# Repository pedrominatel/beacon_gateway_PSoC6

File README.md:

# Beacon Gateway using PSoC6

Beacon Gateway Based on the PSoC6 from CYPRESS

[See this project at Hackaday](https://hackaday.io/project/171521-bluetooth-beacon-proximity-gateway)

### To solve the TLS Proxy error on Ubuntu 20.04 see the link below:

[Use this as starting point](https://github.com/cypresssemiconductorco/mtb-example-anycloud-ble-multi-beacon/blob/f9b318d08451e1a02660163477f669e5317bccea/configs/app_bt_cfg.c)

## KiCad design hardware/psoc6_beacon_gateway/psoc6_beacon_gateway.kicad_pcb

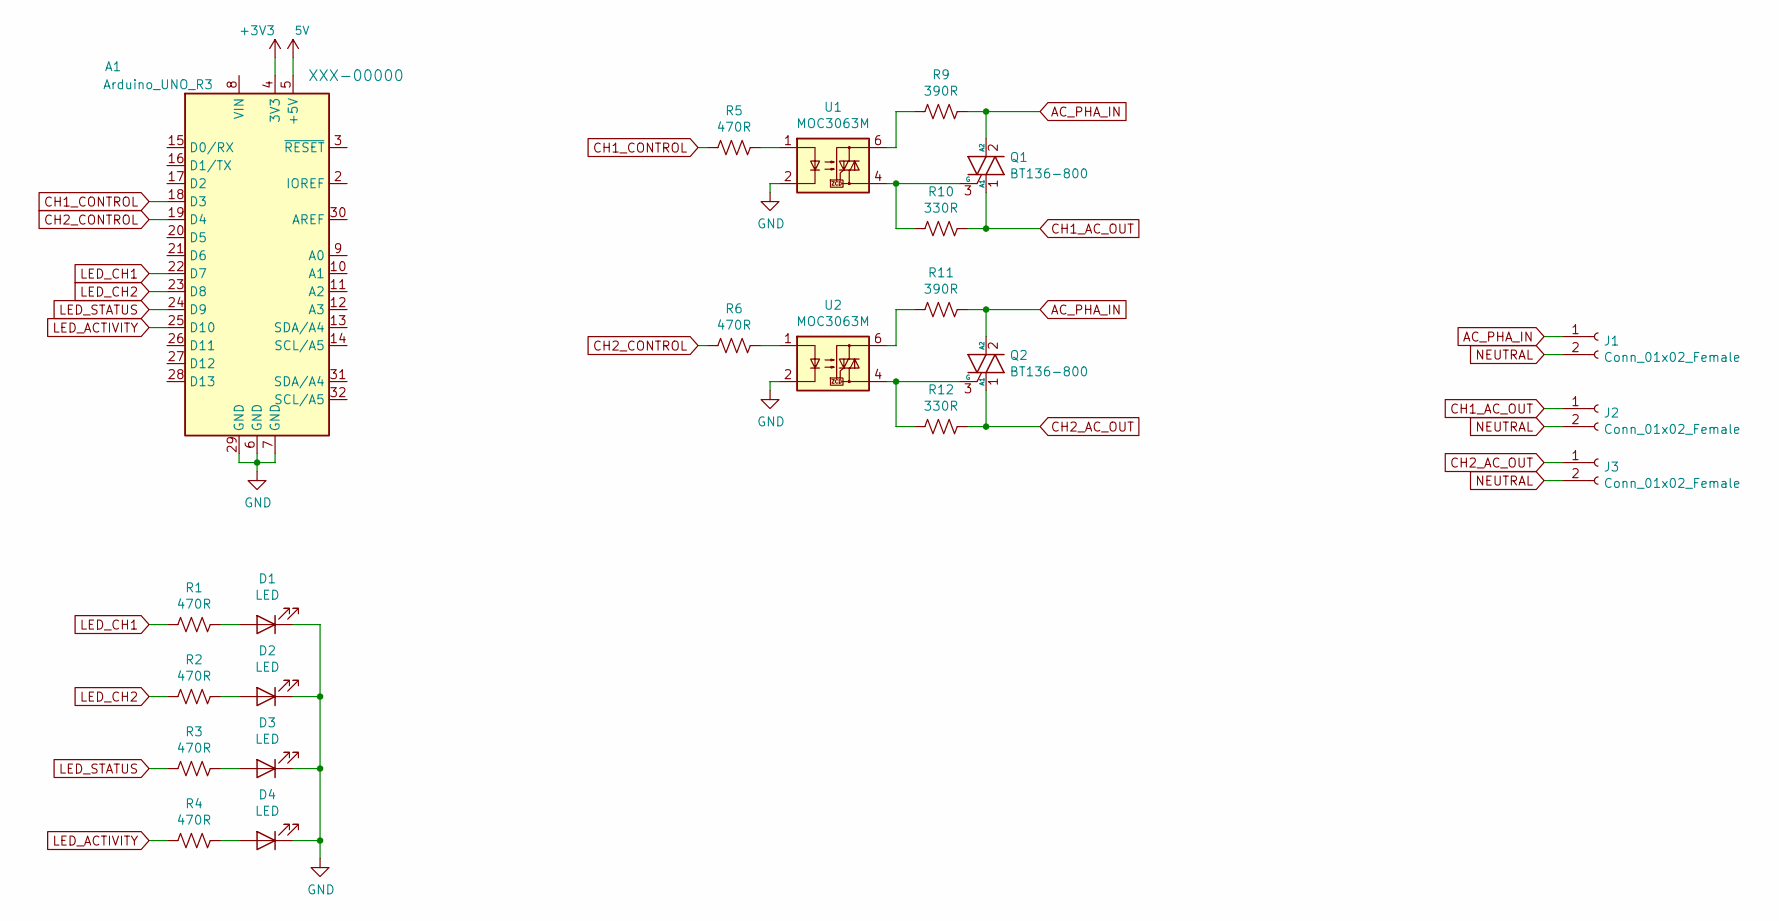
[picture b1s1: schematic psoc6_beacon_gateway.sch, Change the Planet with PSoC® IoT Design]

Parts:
A1: Arduino_UNO_R3
D1, D2, D3, D4: LED; LED_0805_2012Metric
J1, J2, J3: Conn_01x02_Female; PhoenixContact_MC_1,5_2-G-3.5_1x02_P3.50mm_Horizontal
Q1, Q2: BT136-800; TO-252-2
R1, R2, R3, R4, R5, R6: 470R; R_0603_1608Metric
R9, R11: 390R; R_1206_3216Metric
R10, R12: 330R; R_1206_3216Metric
U1, U2: MOC3063M; DIP-6_W8.89mm_SMDSocket_LongPads

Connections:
5V: A1.5 (+5V)
+3V3: A1.4 (3V3)
AC_PHA_IN: J1.1, Q1.2 (A2), Q2.2 (A2), R9.1, R11.1
CH1_AC_OUT: J2.1, Q1.1 (A1), R10.1
CH1_CONTROL: A1.18 (D3), R5.2
CH2_AC_OUT: J3.1, Q2.1 (A1), R12.1
CH2_CONTROL: A1.19 (D4), R6.2
GND: A1.6 (GND), A1.7 (GND), A1.29 (GND), D1.1 (K), D2.1 (K), D3.1 (K), D4.1 (K), U1.2, U2.2
LED_ACTIVITY: A1.25 (D10), R4.2
LED_CH1: A1.22 (D7), R1.2
LED_CH2: A1.23 (D8), R2.2
LED_STATUS: A1.24 (D9), R3.2
NEUTRAL: J1.2, J2.2, J3.2
unnamed: D1.2 (A), R1.1
unnamed: D2.2 (A), R2.1
unnamed: D3.2 (A), R3.1
unnamed: D4.2 (A), R4.1
unnamed: Q1.3 (G), R10.2, U1.4
unnamed: Q2.3 (G), R12.2, U2.4
unnamed: R5.1, U1.1
unnamed: R6.1, U2.1
unnamed: R9.2, U1.6
unnamed: R11.2, U2.6

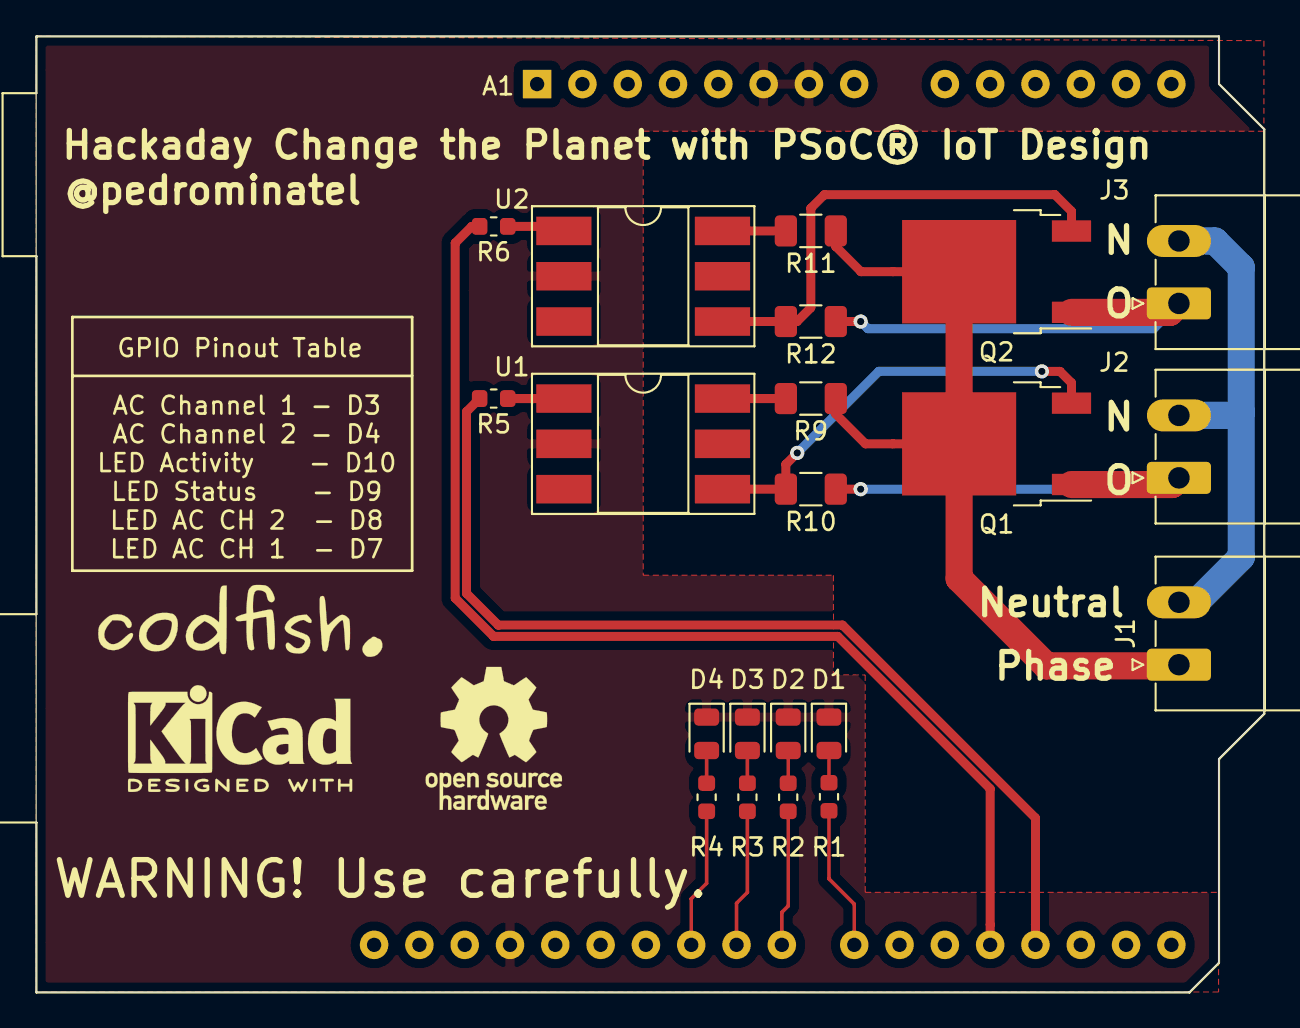
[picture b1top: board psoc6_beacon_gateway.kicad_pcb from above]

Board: 2 copper layers, 68.8 x 53.6 mm, 22 parts (0 on the bottom side), 21 nets.

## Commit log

2020-07-11 Added template/example project as starting point
2020-07-12 Removed files
2020-07-12 main file added
2020-08-01 New features added
2020-08-01 Kicad Project added
2020-08-20 HW first schamatic version
2020-08-20 FW updated
2020-08-23 FW with some issues on BLE and WiFi at same time
2020-08-23 fixed scan issue
2020-08-24 New function added
